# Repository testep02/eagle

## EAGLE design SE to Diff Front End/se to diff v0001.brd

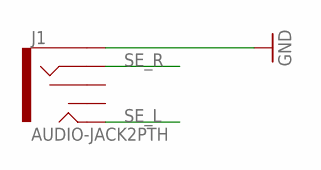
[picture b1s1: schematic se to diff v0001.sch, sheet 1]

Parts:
J1: AUDIO-JACK2PTH; AUDIO-JACK

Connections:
GND: J1.SLEEVE; also elsewhere on the board
SE_L: J1.TIP; also elsewhere on the board
SE_R: J1.RING; also elsewhere on the board

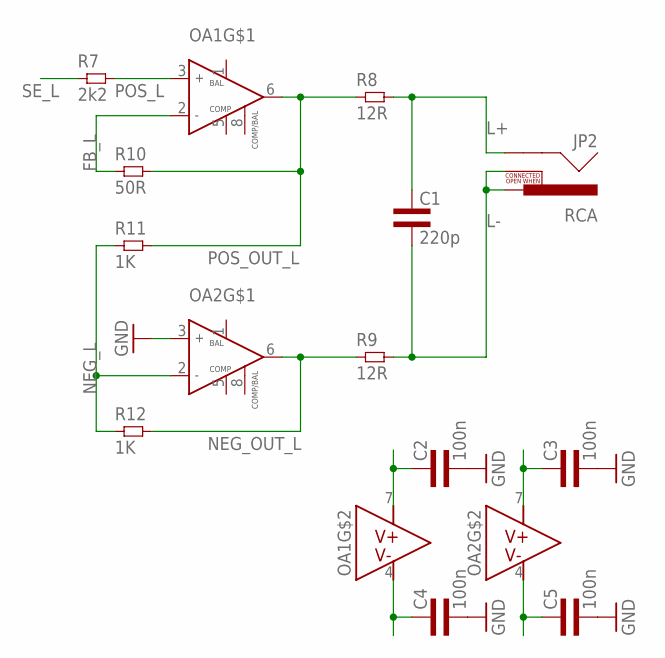
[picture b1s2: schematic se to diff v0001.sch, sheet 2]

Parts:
C1: 220p; 0603L3
C2, C3, C4, C5: 100n; 0603L3
JP2: RCA
OA1, OA2: NE5534DSOIC8; SOIC-8
R7: 2k2; 0603L3
R8, R9: 12R; 0603L3
R10: 50R; 0603L3
R11, R12: 1K; 0603L3

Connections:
FB_L: OA1.2 (IN-), R10.P$1 (1)
GND: C2.P$2 (2), C3.P$2 (2), C4.P$2 (2), C5.P$2 (2), OA2.3 (IN+); also elsewhere on the board
L+: C1.P$1 (1), JP2.SHELL, R8.P$2 (2)
L-: C1.P$2 (2), JP2.PIN, JP2.SWITCH, R9.P$2 (2)
NEG_L: OA2.2 (IN-), R11.P$1 (1), R12.P$1 (1)
NEG_OUT_L: OA2.6 (OUT), R9.P$1 (1), R12.P$2 (2)
POS_L: OA1.3 (IN+), R7.P$2 (2)
POS_OUT_L: OA1.6 (OUT), R8.P$1 (1), R10.P$2 (2), R11.P$2 (2)
SE_L: R7.P$1 (1); also elsewhere on the board
V+: C2.P$1 (1), C3.P$1 (1), OA1.7 (V+), OA2.7 (V+); also elsewhere on the board
V-: C4.P$1 (1), C5.P$1 (1), OA1.4 (V-), OA2.4 (V-); also elsewhere on the board

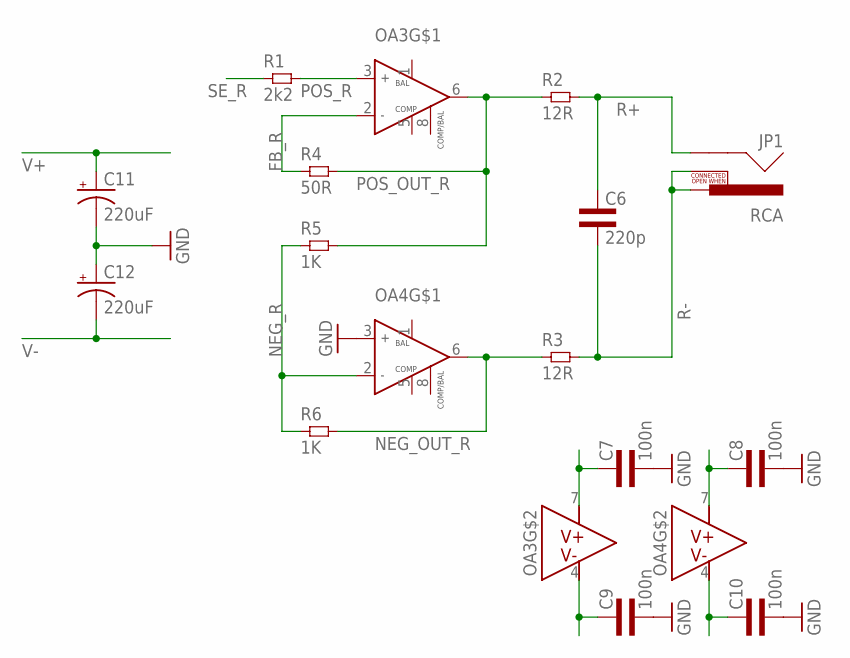
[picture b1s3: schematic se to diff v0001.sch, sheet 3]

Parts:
C6: 220p; 0603L3
C7, C8, C9, C10: 100n; 0603L3
C11, C12: 220uF; CT7343
JP1: RCA
OA3, OA4: NE5534DSOIC8; SOIC-8
R1: 2k2; 0603L3
R2, R3: 12R; 0603L3
R4: 50R; 0603L3
R5, R6: 1K; 0603L3

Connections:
FB_R: OA3.2 (IN-), R4.P$1 (1)
GND: C7.P$2 (2), C8.P$2 (2), C9.P$2 (2), C10.P$2 (2), C11.-, C12.+, OA4.3 (IN+); also elsewhere on the board
NEG_OUT_R: OA4.6 (OUT), R3.P$1 (1), R6.P$2 (2)
NEG_R: OA4.2 (IN-), R5.P$1 (1), R6.P$1 (1)
POS_OUT_R: OA3.6 (OUT), R2.P$1 (1), R4.P$2 (2), R5.P$2 (2)
POS_R: OA3.3 (IN+), R1.P$2 (2)
R+: C6.P$1 (1), JP1.SHELL, R2.P$2 (2)
R-: C6.P$2 (2), JP1.PIN, JP1.SWITCH, R3.P$2 (2)
SE_R: R1.P$1 (1); also elsewhere on the board
V+: C7.P$1 (1), C8.P$1 (1), C11.+, OA3.7 (V+), OA4.7 (V+); also elsewhere on the board
V-: C9.P$1 (1), C10.P$1 (1), C12.-, OA3.4 (V-), OA4.4 (V-); also elsewhere on the board

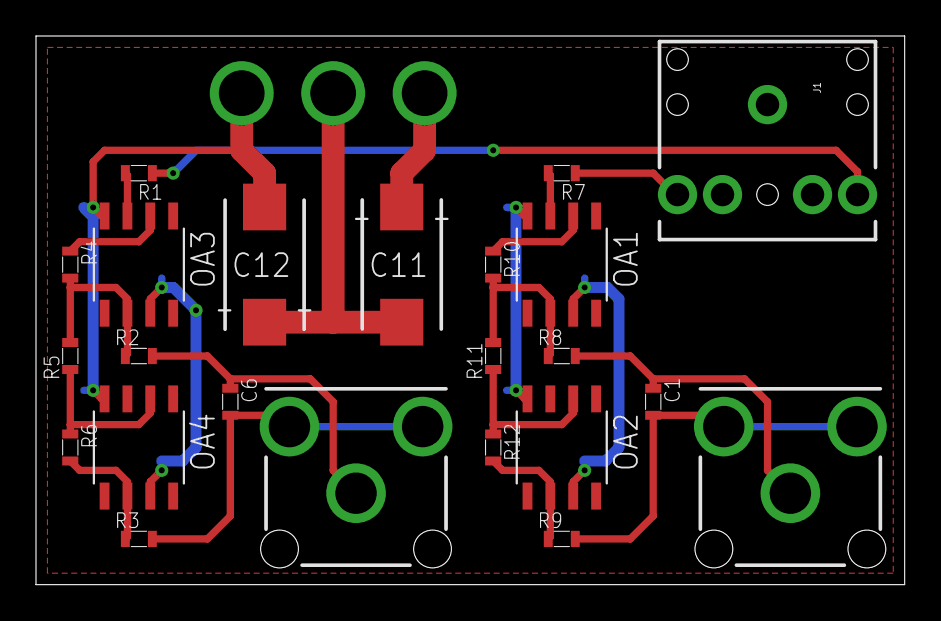
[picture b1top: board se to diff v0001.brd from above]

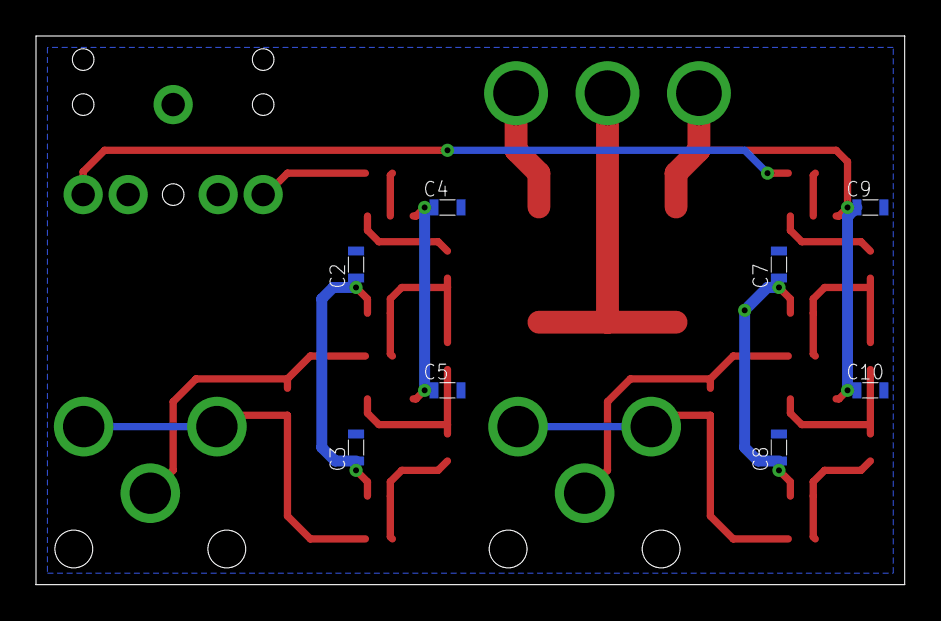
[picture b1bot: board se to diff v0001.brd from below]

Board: 2 copper layers, 48.3 x 30.5 mm, 31 parts (8 on the bottom side), 19 nets.

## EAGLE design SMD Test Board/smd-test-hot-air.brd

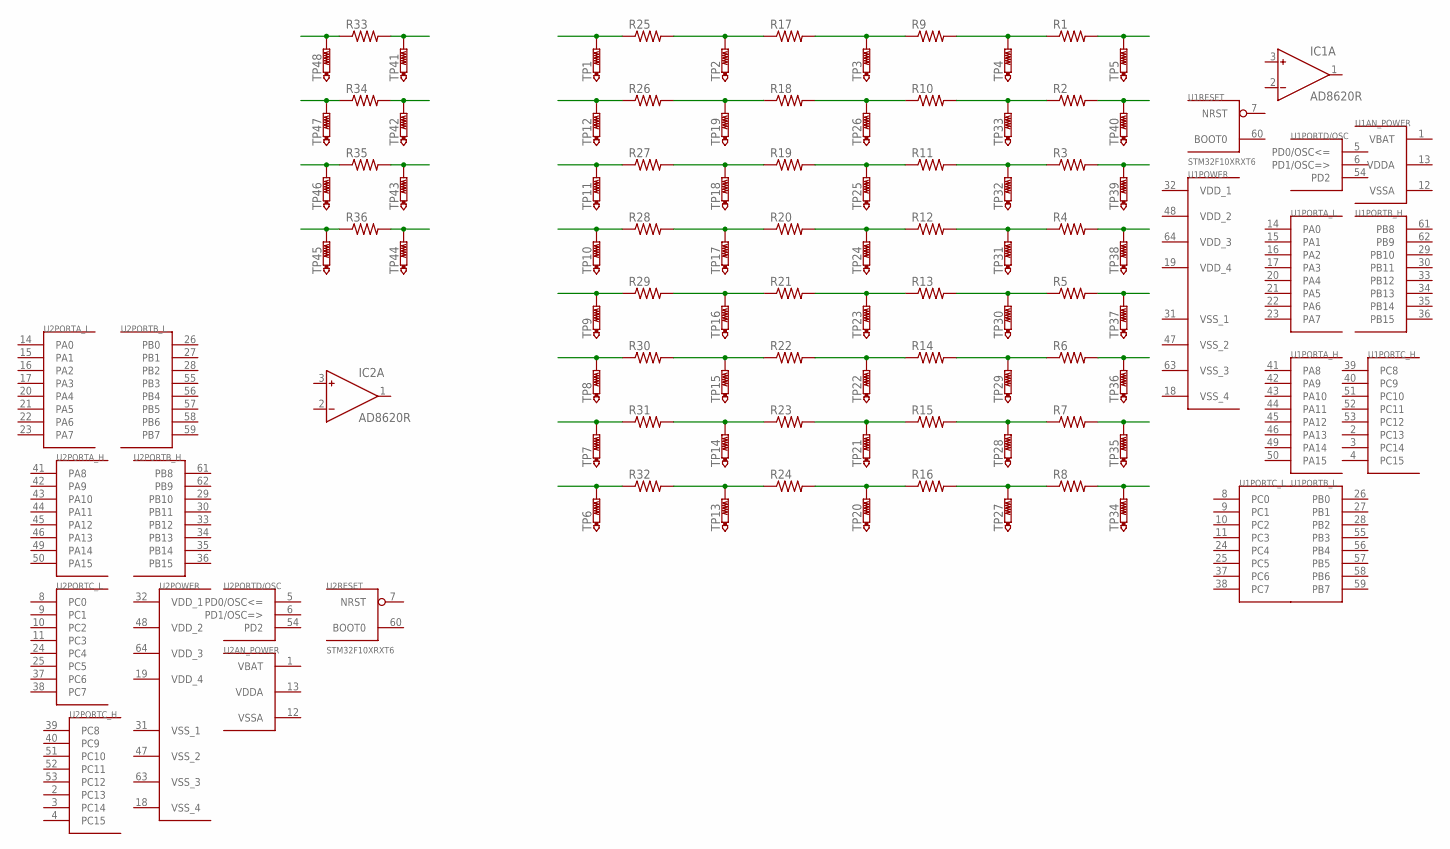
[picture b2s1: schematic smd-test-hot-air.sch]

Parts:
IC1, IC2: AD8620R; SO8
R1, R2, R3, R4, R5, R6, R7, R8: R-US_R0805; R0805
R9, R10, R11, R12, R13, R14, R15, R16: R-US_R0603; R0603
R17, R18, R19, R20, R21, R22, R23, R24: R-US_R0402; R0402
R25, R26, R27, R28, R29, R30, R31, R32: R-US_R0201; R0201
R33, R34, R35, R36: R-US_0204/7; 0204/7
TP1, TP2, TP3, TP4, TP5, TP6, TP7, TP8, TP9, TP10, TP11, TP12, TP13, TP14, TP15, TP16, TP17, TP18, TP19, TP20, TP21, TP22, TP23, TP24, TP25, TP26, TP27, TP28, TP29, TP30, TP31, TP32, TP33, TP34, TP35, TP36, TP37, TP38, TP39, TP40, TP41, TP42, TP43, TP44, TP45, TP46, TP47, TP48: PTR1TP11R; TP11R
U1, U2: STM32F10XRXT6; TQFP64

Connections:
unnamed: R17.1, R25.2, TP2.TP
unnamed: R9.1, R17.2, TP3.TP
unnamed: R1.1, R9.2, TP4.TP
unnamed: R1.2, TP5.TP
unnamed: R25.1, TP1.TP
unnamed: R26.1, TP12.TP
unnamed: R27.1, TP11.TP
unnamed: R28.1, TP10.TP
unnamed: R29.1, TP9.TP
unnamed: R30.1, TP8.TP
unnamed: R31.1, TP7.TP
unnamed: R32.1, TP6.TP
unnamed: R2.2, TP40.TP
unnamed: R3.2, TP39.TP
unnamed: R4.2, TP38.TP
unnamed: R5.2, TP37.TP
unnamed: R6.2, TP36.TP
unnamed: R7.2, TP35.TP
unnamed: R8.2, TP34.TP
unnamed: R8.1, R16.2, TP27.TP
unnamed: R7.1, R15.2, TP28.TP
unnamed: R6.1, R14.2, TP29.TP
unnamed: R5.1, R13.2, TP30.TP
unnamed: R4.1, R12.2, TP31.TP
unnamed: R3.1, R11.2, TP32.TP
unnamed: R2.1, R10.2, TP33.TP
unnamed: R10.1, R18.2, TP26.TP
unnamed: R11.1, R19.2, TP25.TP
unnamed: R12.1, R20.2, TP24.TP
unnamed: R13.1, R21.2, TP23.TP
unnamed: R14.1, R22.2, TP22.TP
unnamed: R15.1, R23.2, TP21.TP
unnamed: R16.1, R24.2, TP20.TP
unnamed: R18.1, R26.2, TP19.TP
unnamed: R19.1, R27.2, TP18.TP
unnamed: R20.1, R28.2, TP17.TP
unnamed: R21.1, R29.2, TP16.TP
unnamed: R22.1, R30.2, TP15.TP
unnamed: R23.1, R31.2, TP14.TP
unnamed: R24.1, R32.2, TP13.TP
unnamed: R33.2, TP41.TP
unnamed: R34.2, TP42.TP
unnamed: R35.2, TP43.TP
unnamed: R36.2, TP44.TP
unnamed: R33.1, TP48.TP
unnamed: R34.1, TP47.TP
unnamed: R35.1, TP46.TP
unnamed: R36.1, TP45.TP
V+: IC1.8 (V+), IC2.8 (V+)
V-: IC1.4 (V-), IC2.4 (V-)
VBAT: U1.1 (VBAT), U2.1 (VBAT)
VDDA: U1.13 (VDDA), U2.13 (VDDA)
VDD_1: U1.32 (VDD_1), U2.32 (VDD_1)
VDD_2: U1.48 (VDD_2), U2.48 (VDD_2)
VDD_3: U1.64 (VDD_3), U2.64 (VDD_3)
VDD_4: U1.19 (VDD_4), U2.19 (VDD_4)
VSSA: U1.12 (VSSA), U2.12 (VSSA)
VSS_1: U1.31 (VSS_1), U2.31 (VSS_1)
VSS_2: U1.47 (VSS_2), U2.47 (VSS_2)
VSS_3: U1.63 (VSS_3), U2.63 (VSS_3)
VSS_4: U1.18 (VSS_4), U2.18 (VSS_4)

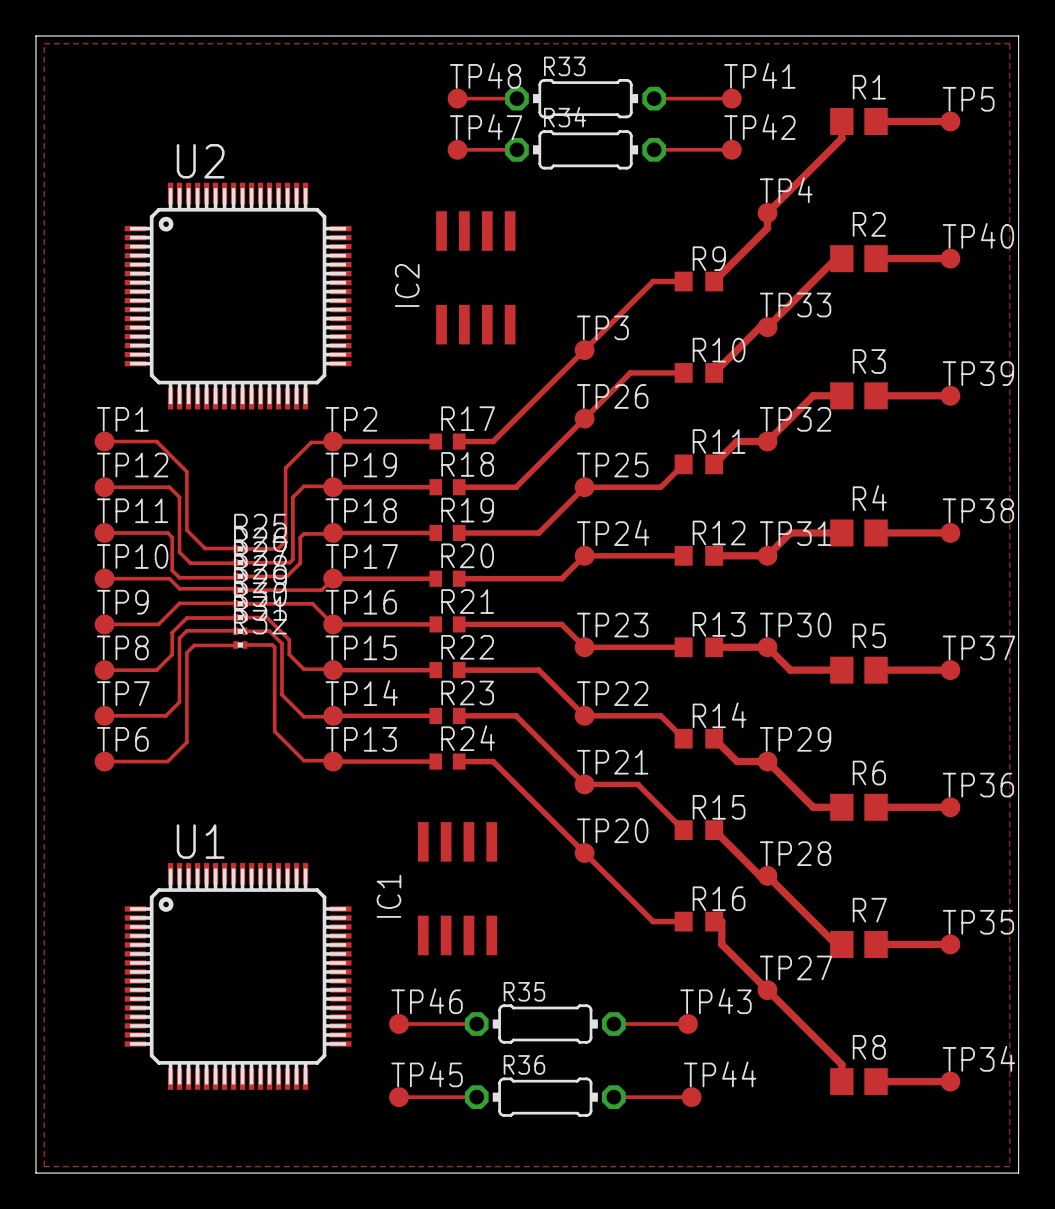
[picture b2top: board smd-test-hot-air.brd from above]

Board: 2 copper layers, 54.6 x 63.2 mm, 88 parts (0 on the bottom side), 61 nets.

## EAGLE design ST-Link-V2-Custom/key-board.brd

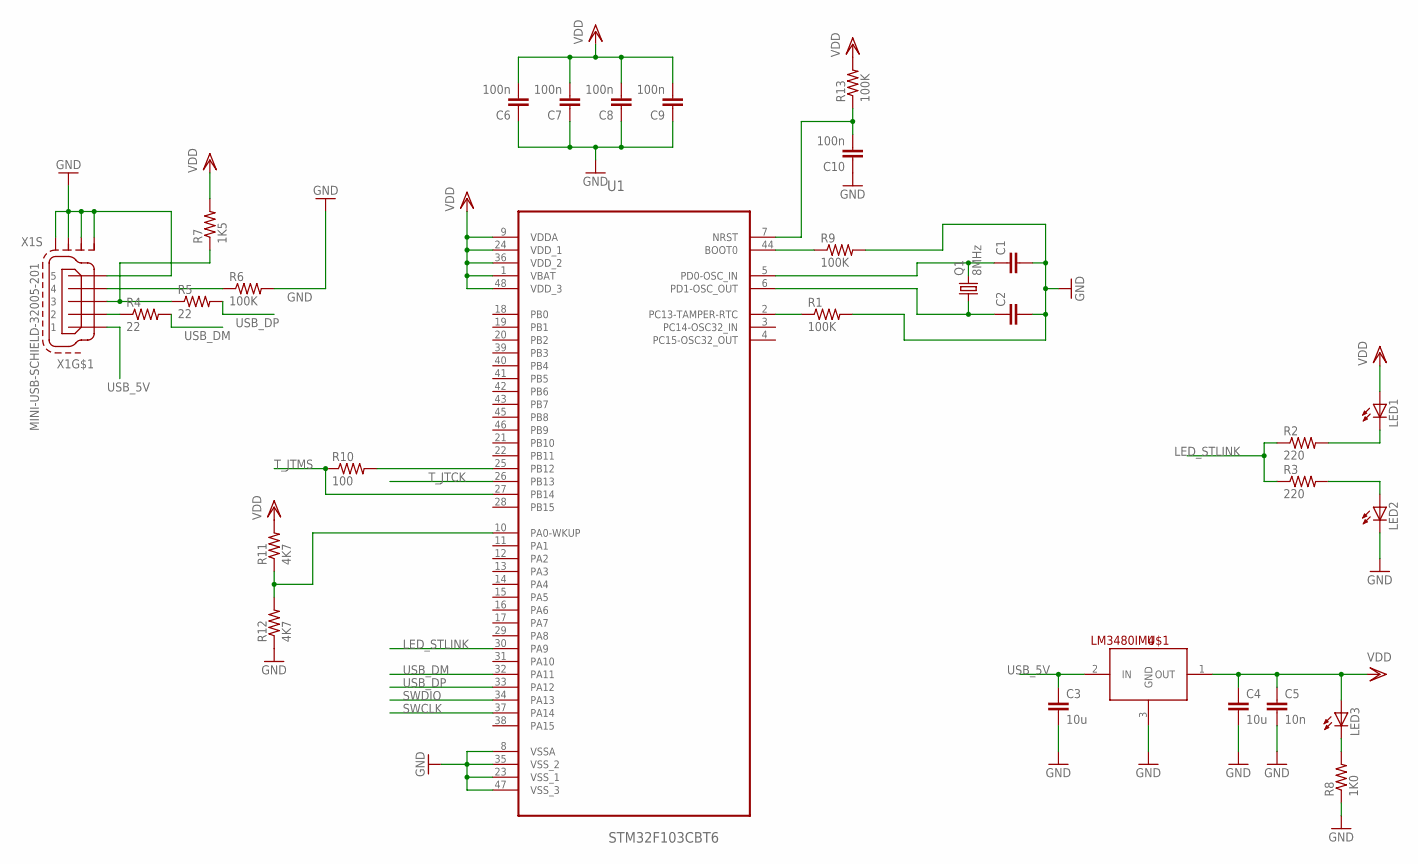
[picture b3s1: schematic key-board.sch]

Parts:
C1, C2: C-EUC0402; C0402
C3, C4: 10u; C0805
C5: 10n; C0402
C6, C7, C8, C9, C10: 100n; C0402
LED1, LED2, LED3: LEDCHIPLED-0603-TTW; CHIPLED-0603-TTW
Q1: 8MHz; HC49U-V
R1, R6, R9, R13: 100K; R0402
R2, R3: 220; R0402
R4, R5: 22; R0402
R7: 1K5; R0402
R8: 1K0; R0402
R10: 100; R0402
R11, R12: 4K7; R0402
U1: STM32F103CBT6; QFP50P900X900X160-48N
U$1: LM3480IM4; SOT23-3
X1: MINI-USB-SCHIELD-32005-201; 32005-201

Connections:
GND: C1.2, C2.2, C3.2, C4.2, C5.2, C6.1, C7.1, C8.1, C9.1, C10.1, LED2.C@1 (C), R1.2, R6.2, R8.1, R9.2, R12.1, U1.8 (VSSA), U1.23 (VSS_1), U1.35 (VSS_2), U1.47 (VSS_3), U$1.3 (GND), X1.5, X1.M1 (S1), X1.M2 (S2), X1.M3 (S3), X1.M4 (S4)
LED_STLINK: R2.1, R3.1, U1.30 (PA9)
unnamed: C1.1, Q1.2, U1.5 (PD0-OSC_IN)
unnamed: C2.1, Q1.1, U1.6 (PD1-OSC_OUT)
unnamed: R6.1, X1.4
unnamed: R1.1, U1.2 (PC13-TAMPER-RTC)
unnamed: LED1.C@1 (C), R2.2
unnamed: LED2.A@1 (A), R3.2
unnamed: R5.1, R7.1, X1.3
unnamed: R4.1, X1.2
unnamed: LED3.C@1 (C), R8.2
unnamed: R11.1, R12.2, U1.10 (PA0-WKUP)
unnamed: C10.2, R13.1, U1.7 (NRST)
unnamed: R9.1, U1.44 (BOOT0)
unnamed: R10.2, U1.25 (PB12)
SWCLK: U1.37 (PA14)
SWDIO: U1.34 (PA13)
T_JTCK: U1.26 (PB13)
T_JTMS: R10.1, U1.27 (PB14)
USB_5V: C3.1, U$1.2 (IN), X1.1
USB_DM: R4.2, U1.32 (PA11)
USB_DP: R5.2, U1.33 (PA12)
VDD: C4.1, C5.1, C6.2, C7.2, C8.2, C9.2, LED1.A@1 (A), LED3.A@1 (A), R7.2, R11.2, R13.2, U1.1 (VBAT), U1.9 (VDDA), U1.24 (VDD_1), U1.36 (VDD_2), U1.48 (VDD_3), U$1.1 (OUT)

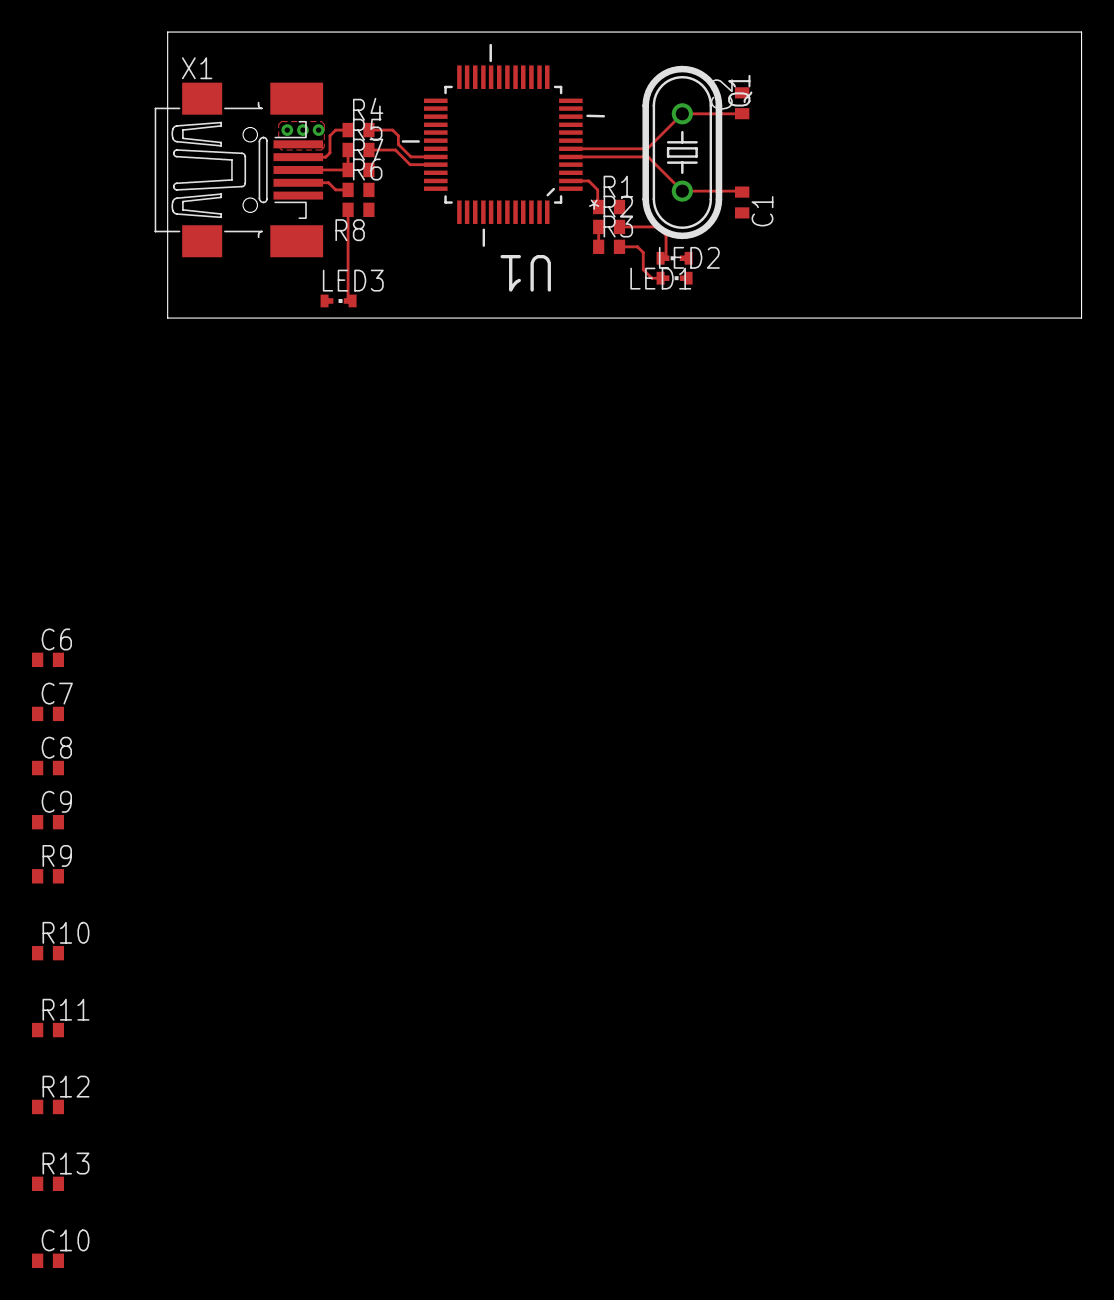
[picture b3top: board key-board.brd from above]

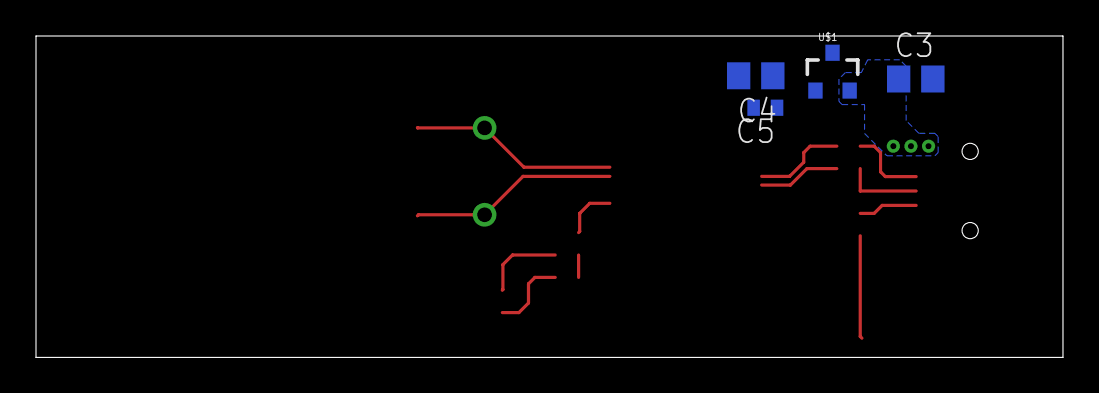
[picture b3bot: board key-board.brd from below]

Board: 2 copper layers, 57.1 x 17.9 mm, 30 parts (4 on the bottom side), 20 nets.

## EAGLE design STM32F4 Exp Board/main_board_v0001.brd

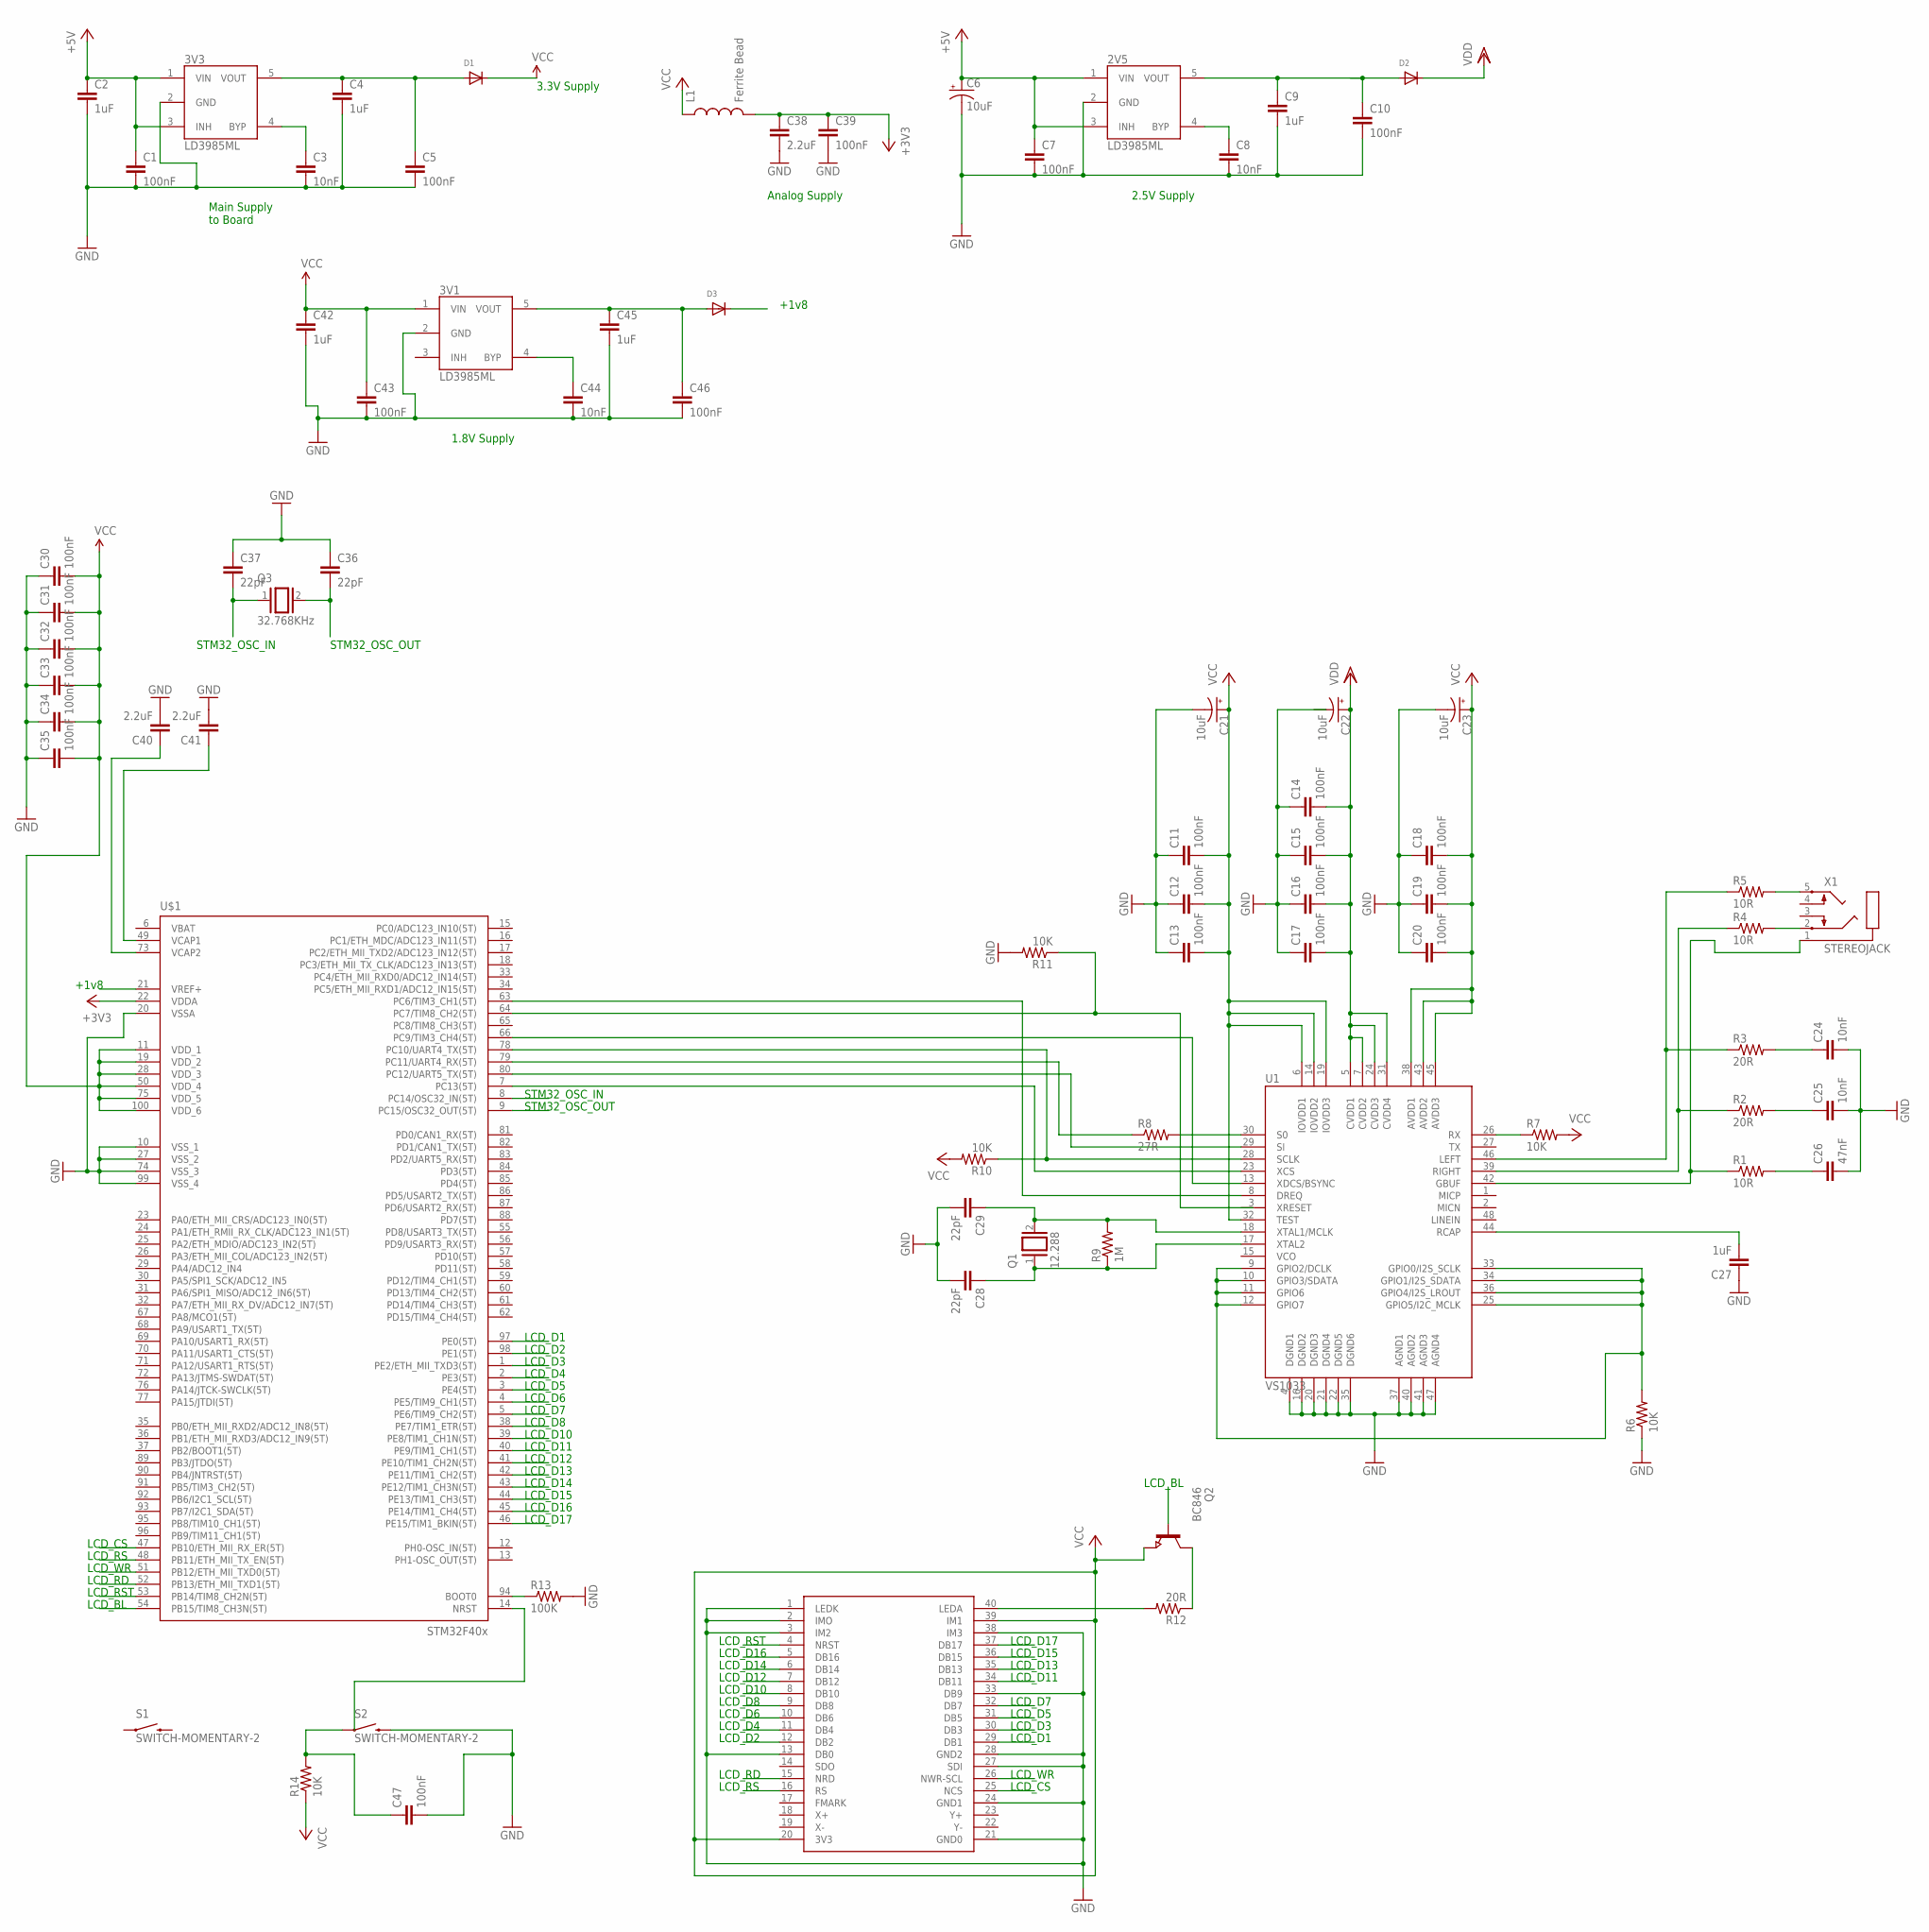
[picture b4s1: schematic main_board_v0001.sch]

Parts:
2V5, 3V1, 3V3: LD3985ML; SOT-23-5L
C1, C5, C7, C30, C31, C32, C33, C34, C35, C39, C43, C46: 100nF; C1005
C2, C4, C9, C27, C42, C45: 1uF; C0603
C3, C8, C24, C25, C44: 10nF; C0603
C6, C21, C22, C23: 10uF; EIA3528-KIT
C10: 100nF; C1005@1
C11, C12, C13, C14, C15, C16, C17, C18, C19, C20, C47: 100nF; C0603
C26: 47nF; C0603
C28, C29: 22pF; C0603
C36, C37: 22pF; C1005
C38, C40, C41: 2.2uF; C1005
D1, D2, D3: DIODESOD-323F; SOD-323F
L1: Ferrite Bead; C0402
Q1: 12.288; QS
Q2: BC846; SOT23
Q3: 32.768KHz; QS
R1, R4, R5: 10R; M0805
R2, R3, R12: 20R; M0805
R6, R7, R10, R11, R14: 10K; M0805
R8: 27R; M0805
R9: 1M; M0805
R13: 100K; M0805
S1, S2: SWITCH-MOMENTARY-2; TACTILE_SWITCH_TALL
U1: VS1033; LQFP-48
U$1: STM32F407V; TQFP100
U$2: MIKROE-PROTO-ILI9341; 2X20-PINHEAD
X1: STEREOJACK; STX3100

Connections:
+1V8: D3.C, U$1.21 (VREF+)
+3V3: C38.1, C39.1, L1.2, U$1.22 (VDDA)
+5V: 2V5.1 (VIN), 2V5.3 (INH), 3V3.1 (VIN), 3V3.3 (INH), C1.1, C2.1, C6.A (+), C7.1
GND: 2V5.2 (GND), 3V1.2 (GND), 3V3.2 (GND), C1.2, C2.2, C3.2, C4.2, C5.2, C6.C (-), C7.2, C8.2, C9.2, C10.2, C11.1, C12.1, C13.1, C14.1, C15.1, C16.1, C17.1, C18.1, C19.1, C20.1, C21.C (-), C23.C (-), C24.2, C25.2, C26.2, C27.1, C28.2, C29.2, C30.1, C31.1, C32.1, C33.1, C34.1, C35.1, C36.1, C37.1, C38.2, C39.2, C40.2, C41.2, C42.2, C43.2, C44.2, C45.2, C46.2, C47.2, R6.1, R11.2, R13.2, S2.B2 (2), U1.4 (DGND1), U1.16 (DGND2), U1.20 (DGND3), U1.21 (DGND4), U1.22 (DGND5), U1.35 (DGND6), U1.37 (AGND1), U1.40 (AGND2), U1.41 (AGND3), U1.47 (AGND4), U$1.10 (VSS_1), U$1.20 (VSSA), U$1.27 (VSS_2), U$1.74 (VSS_3), U$1.99 (VSS_4), U$2.1 (LEDK), U$2.2 (IMO), U$2.3 (IM2), U$2.13 (DB0), U$2.21 (GND0), U$2.24 (GND1), U$2.27 (SDI), U$2.28 (GND2), U$2.33 (DB9), U$2.38 (IM3)
LCD_BL: Q2.1 (B), U$1.54 (PB15/TIM8_CH3N(5T))
LCD_CS: U$1.47 (PB10/ETH_MII_RX_ER(5T)), U$2.25 (NCS)
LCD_D1: U$1.97 (PE0(5T)), U$2.29 (DB1)
LCD_D2: U$1.98 (PE1(5T)), U$2.12 (DB2)
LCD_D3: U$1.1 (PE2/ETH_MII_TXD3(5T)), U$2.30 (DB3)
LCD_D4: U$1.2 (PE3(5T)), U$2.11 (DB4)
LCD_D5: U$1.3 (PE4(5T)), U$2.31 (DB5)
LCD_D6: U$1.4 (PE5/TIM9_CH1(5T)), U$2.10 (DB6)
LCD_D7: U$1.5 (PE6/TIM9_CH2(5T)), U$2.32 (DB7)
LCD_D8: U$1.38 (PE7/TIM1_ETR(5T)), U$2.9 (DB8)
LCD_D10: U$1.39 (PE8/TIM1_CH1N(5T)), U$2.8 (DB10)
LCD_D11: U$1.40 (PE9/TIM1_CH1(5T)), U$2.34 (DB11)
LCD_D12: U$1.41 (PE10/TIM1_CH2N(5T)), U$2.7 (DB12)
LCD_D13: U$1.42 (PE11/TIM1_CH2(5T)), U$2.35 (DB13)
LCD_D14: U$1.43 (PE12/TIM1_CH3N(5T)), U$2.6 (DB14)
LCD_D15: U$1.44 (PE13/TIM1_CH3(5T)), U$2.36 (DB15)
LCD_D16: U$1.45 (PE14/TIM1_CH4(5T)), U$2.5 (DB16)
LCD_D17: U$1.46 (PE15/TIM1_BKIN(5T)), U$2.37 (DB17)
LCD_RD: U$1.52 (PB13/ETH_MII_TXD1(5T)), U$2.15 (NRD)
LCD_RS: U$1.48 (PB11/ETH_MII_TX_EN(5T)), U$2.16 (RS)
LCD_RST: U$1.53 (PB14/TIM8_CH2N(5T)), U$2.4 (NRST)
LCD_WR: U$1.51 (PB12/ETH_MII_TXD0(5T)), U$2.26 (NWR-SCL)
unnamed: 2V5.5 (VOUT), C9.1, C10.1, D2.A
unnamed: R1.1, U1.42 (GBUF), X1.1
unnamed: 2V5.4 (BYP), C8.1
unnamed: 3V3.4 (BYP), C3.1
unnamed: R2.1, R4.1, U1.39 (RIGHT)
unnamed: 3V3.5 (VOUT), C4.1, C5.1, D1.A
unnamed: R3.1, R5.1, U1.46 (LEFT)
unnamed: C26.1, R1.2
unnamed: C25.1, R2.2
unnamed: C24.1, R3.2
unnamed: R4.2, X1.2
unnamed: R5.2, X1.5
unnamed: R8.2, U1.30 (S0)
unnamed: C27.2, U1.44 (RCAP)
unnamed: R6.2, U1.9 (GPIO2/DCLK), U1.10 (GPIO3/SDATA), U1.11 (GPIO6), U1.12 (GPIO7), U1.25 (GPIO5/I2C_MCLK), U1.33 (GPIO0/I2S_SCLK), U1.34 (GPIO1/I2S_SDATA), U1.36 (GPIO4/I2S_LROUT)
unnamed: R7.1, U1.26 (RX)
unnamed: R10.1, U1.28 (SCLK), U$1.78 (PC10/UART4_TX(5T))
unnamed: R8.1, U$1.79 (PC11/UART4_RX(5T))
unnamed: U1.29 (SI), U$1.80 (PC12/UART5_TX(5T))
unnamed: U1.23 (XCS), U$1.7 (PC13(5T))
unnamed: U1.13 (XDCS/BSYNC), U$1.66 (PC9/TIM3_CH4(5T))
unnamed: R11.1, U$1.64 (PC7/TIM8_CH2(5T))
unnamed: U1.8 (DREQ), U$1.63 (PC6/TIM3_CH1(5T))
unnamed: C28.1, Q1.1, R9.1, U1.17 (XTAL2)
unnamed: C29.1, Q1.2, R9.2, U1.18 (XTAL1/MCLK)
unnamed: C40.1, U$1.73 (VCAP2)
unnamed: Q2.3 (C), R12.1
unnamed: R12.2, U$2.40 (LEDA)
unnamed: C41.1, U$1.49 (VCAP1)
unnamed: R13.1, U$1.94 (BOOT0)
unnamed: 3V1.4 (BYP), C44.1
unnamed: C47.1, R14.2, S2.A2 (1)
unnamed: 3V1.5 (VOUT), C45.1, C46.1, D3.A
STM32_OSC_IN: C37.2, Q3.1, U$1.8 (PC14/OSC32_IN(5T))
STM32_OSC_OUT: C36.2, Q3.2, U$1.9 (PC15/OSC32_OUT(5T))
VCC: 3V1.1 (VIN), C11.2, C12.2, C13.2, C18.2, C19.2, C20.2, C21.A (+), C23.A (+), C30.2, C31.2, C32.2, C33.2, C34.2, C35.2, C42.1, C43.1, D1.C, L1.1, Q2.2 (E), R7.2, R10.2, R14.1, U1.6 (IOVDD1), U1.14 (IOVDD2), U1.19 (IOVDD3), U1.32 (TEST), U1.38 (AVDD1), U1.43 (AVDD2), U1.45 (AVDD3), U$1.11 (VDD_1), U$1.19 (VDD_2), U$1.28 (VDD_3), U$1.50 (VDD_4), U$1.75 (VDD_5), U$1.100 (VDD_6), U$2.20 (3V3), U$2.39 (IM1)
VDD: C14.2, C15.2, C16.2, C17.2, C22.A (+), D2.C, U1.5 (CVDD1), U1.7 (CVDD2), U1.24 (CVDD3), U1.31 (CVDD4)

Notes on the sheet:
Main Supply to Board
3.3V Supply
2.5V Supply
LCD_D1
LCD_D2
LCD_D3
LCD_D4
LCD_D5
LCD_D6
LCD_D7
LCD_D8
LCD_D10
LCD_D11
LCD_D12
LCD_D13
LCD_D14
LCD_D15
LCD_D16
LCD_D17
LCD_CS
LCD_RS
LCD_WR
LCD_RD
LCD_RST
LCD_BL
STM32_OSC_IN
STM32_OSC_OUT
Analog Supply
+1v8
1.8V Supply

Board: 2 copper layers, 77 parts (0 on the bottom side), 63 nets, no tracks yet.

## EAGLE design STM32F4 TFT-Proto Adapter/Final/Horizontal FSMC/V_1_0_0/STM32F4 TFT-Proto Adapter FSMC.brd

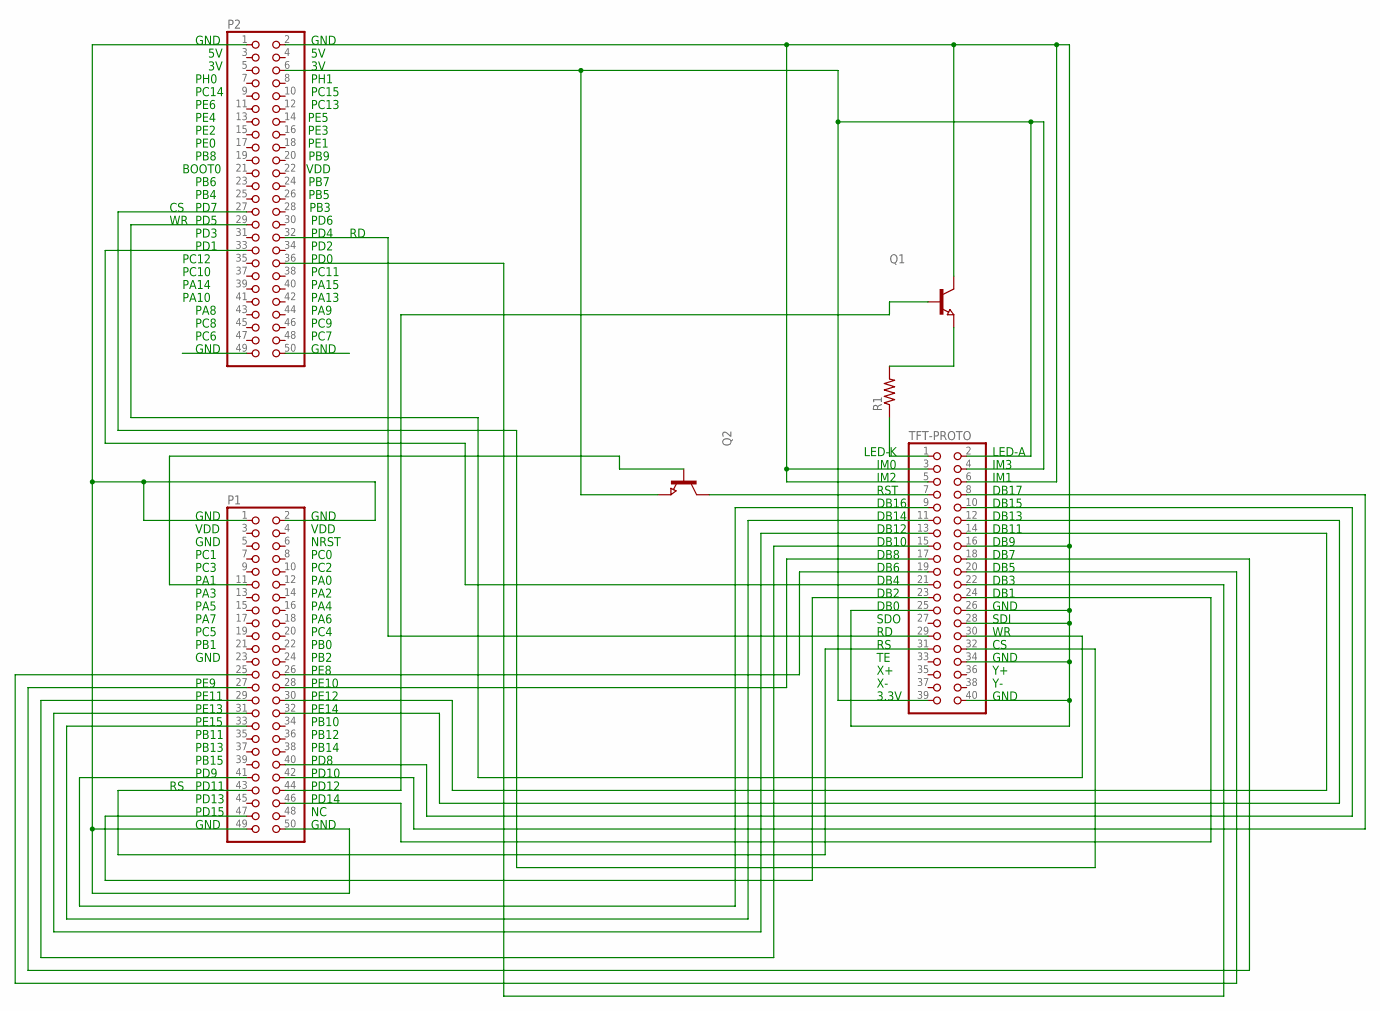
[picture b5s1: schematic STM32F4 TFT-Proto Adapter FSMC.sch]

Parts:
P1, P2: PINHD-2X25; 2X25
Q1, Q2: NPN-TRANSISTOR_SOT23; SOT23
R1: R-US_R0805; R0805
TFT-PROTO: PINHD-2X20; 2X20

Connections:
CS: P2.27, TFT-PROTO.32
DB1: P1.46, TFT-PROTO.24
DB2: P1.47, TFT-PROTO.23
DB3: P2.36, TFT-PROTO.22
DB4: P2.33, TFT-PROTO.21
DB5: P1.25, TFT-PROTO.20
DB6: P1.26, TFT-PROTO.19
DB7: P1.27, TFT-PROTO.18
DB8: P1.28, TFT-PROTO.17
DB10: P1.29, TFT-PROTO.15
DB11: P1.30, TFT-PROTO.14
DB12: P1.31, TFT-PROTO.13
DB13: P1.32, TFT-PROTO.12
DB14: P1.33, TFT-PROTO.11
DB15: P1.40, TFT-PROTO.10
DB16: P1.41, TFT-PROTO.9
DB17: P1.42, TFT-PROTO.8
GND: P1.1, P1.2, P1.49, P1.50, P2.1, P2.2, P2.49, P2.50, Q1.3 (C), TFT-PROTO.3, TFT-PROTO.5, TFT-PROTO.6, TFT-PROTO.16, TFT-PROTO.25, TFT-PROTO.26, TFT-PROTO.28, TFT-PROTO.34, TFT-PROTO.40
unnamed: P1.44, Q1.1 (B)
unnamed: Q1.2 (E), R1.2
unnamed: R1.1, TFT-PROTO.1
unnamed: Q2.3 (C), TFT-PROTO.7
PWR: P2.6, Q2.2 (E), TFT-PROTO.2, TFT-PROTO.4, TFT-PROTO.39
RD: P2.32, TFT-PROTO.29
RS: P1.43, TFT-PROTO.31
RST: P1.11, Q2.1 (B)
WR: P2.29, TFT-PROTO.30

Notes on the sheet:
GND
PH0
PH1
PC14
PC15
PE6
PC13
PE4 PE5
PE2 PE3
PE0 PE1
PB8 PB9
BOOT0 VDD
PB6 PB7
PB4 PB5
PD7 PB3
PD5
PD3
PD1
PC12
PC10
PA14
PA10
PA8
PC8
PC6
PC7
PC9
PA9
PA13
PA15
PC11
PD0
PD2
PD4
PD6
PD15
PD13
PD11
PD9
PB15

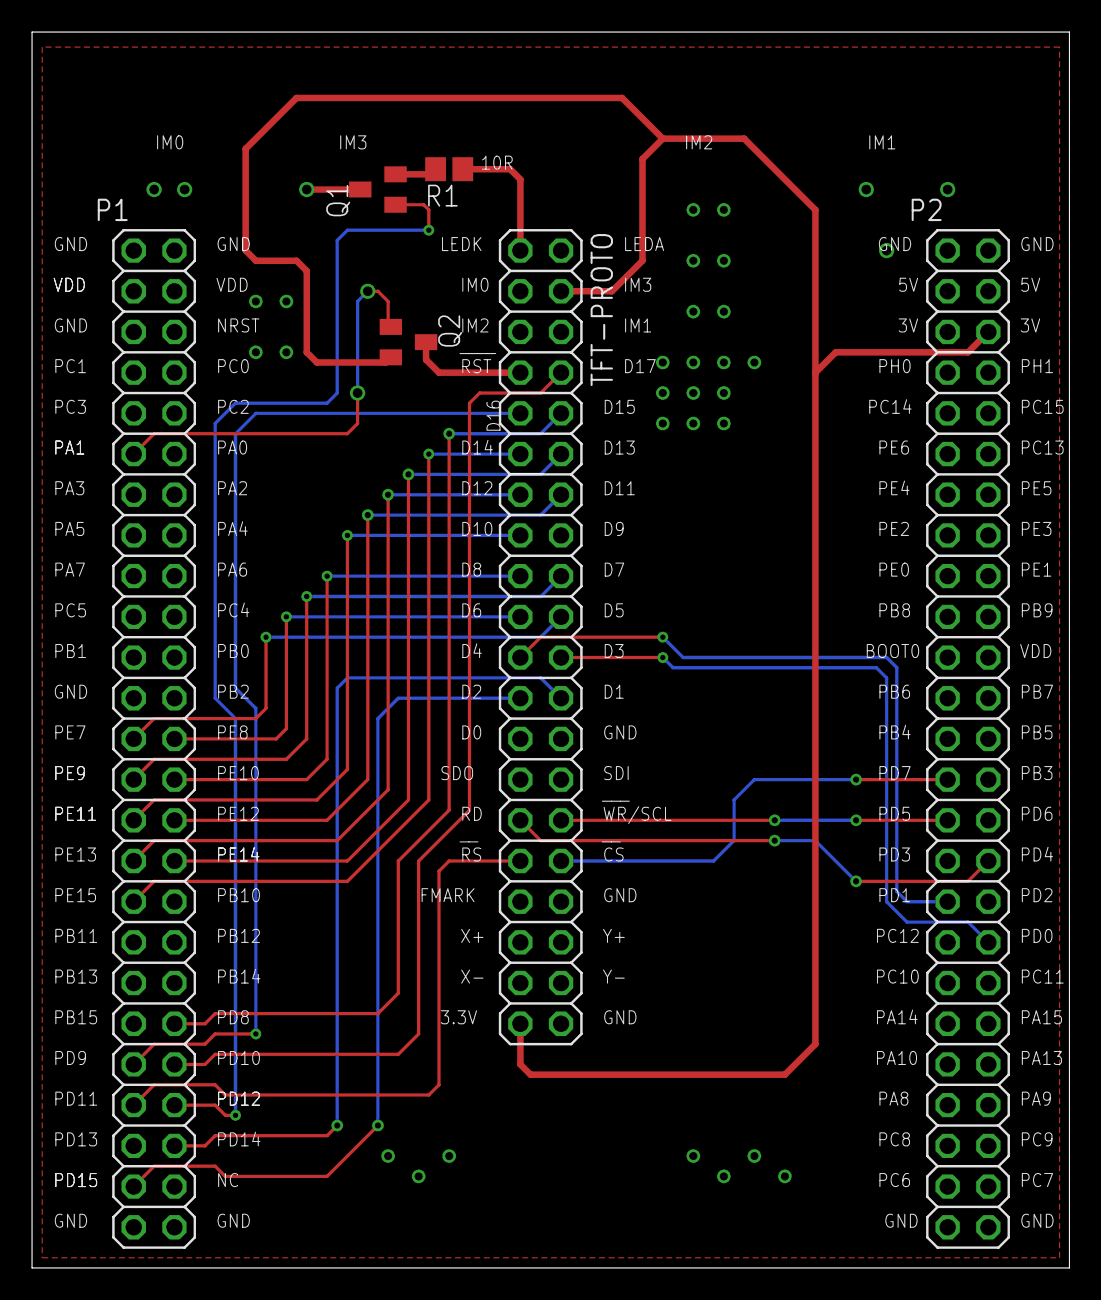
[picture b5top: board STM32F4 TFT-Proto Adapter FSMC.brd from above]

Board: 2 copper layers, 64.8 x 77.1 mm, 6 parts (0 on the bottom side), 27 nets.

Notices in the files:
parts and their libraries:
SparkFun-Connectors: Licensing: CC v3.0 Share-Alike You are welcome to use this library for commercial purposes.
